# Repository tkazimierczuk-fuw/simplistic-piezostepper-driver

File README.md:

# A Simplistic Driver for Slip-Stick Piezo Positioners

This project presents a minimalistic, low-cost driver for slip-stick piezo positioners.

Conventional slip-stick piezo drivers typically rely on operational amplifiers to generate sawtooth waveforms. While this approach gives the most control over the stage, driving highly capacitive piezo loads with op-amps requires careful compensation and layout to avoid instability and self-oscillations.

In contrast, this driver avoids operational amplifiers altogether. Instead, the piezo load is driven directly using simple MOSFET stages. This significantly simplifies the circuit and improves robustness when dealing with capacitive loads, making the design well suited for ad-hoc, experimental, or budget-constrained setups.

The goal of this project is not ultimate performance, but practicality: providing a straightforward and reliable way to generate slip-stick drive signals with minimal component count and design overhead.

## Usage

The driver is straightforward - just connect your slip-stick piezo stage and use 3-way lever-switch to jog the stage. The step amplitude is fixed at 28 V and the step frequency is fixed (in the firmware) at 300 Hz. This values are suitable, e.g. for Attocube ANP series.

The circuit contains a PPTC resettable fuse which trips when we try to drive the short-circuit. It automatically resets upon switching the device off. 

## How it works

The driver generates the characteristic slip-stick waveform by charging and discharging the piezo capacitance directly through MOSFET switches, rather than through linear amplifiers. One stage provides a relatively slow voltage ramp (stick phase), while the other rapidly discharges the piezo (slip phase). Rapid charge/discharge is realized by linking the piezo to VCC/GND directly by a MOSFET. Slow ramp is realized by introducing an extra resistor R in series with the MOSFET. The time-constant of the slope is governed by a product of resistance R and the capacitance of the piezo stage.

Each of 3 modules has the same design:

## What to buy (typical components)

Exact values and footprints are given in the schematics/PCB files, but the design generally requires only common parts:

- 12x N-channel MOSFETs, e.g. STP55NF06L
- 6x half-bridge driver, e.g. IR2104STRPBF
- 3x BNC connector, e.g. R-128
- 3x lever switch, e.g. 1-1825139-8
- 1x power switch, e.g. R13-220BA-01-BBG (oversized)
- Raspberry Pico
- SMD 1206 elements: 7x diode, resistors: 1x 1MΩ, 6x 100kΩ, 12x 22Ω, 3x 10kΩ
- THT capacitors
- a polymer fuse, e.g. 0ZCJ0020FF2E
- DC supply socket, e.g. PJ-063AH
- step-up converter, e.g. MT3608 

## License & Disclaimer

This project is released under the MIT License. You are free to use, modify, and distribute it according to the terms of that license.

The design is provided as-is, without any warranties or guarantees of performance, safety, or suitability for any particular purpose. This is a research/DIY project; use it at your own risk.

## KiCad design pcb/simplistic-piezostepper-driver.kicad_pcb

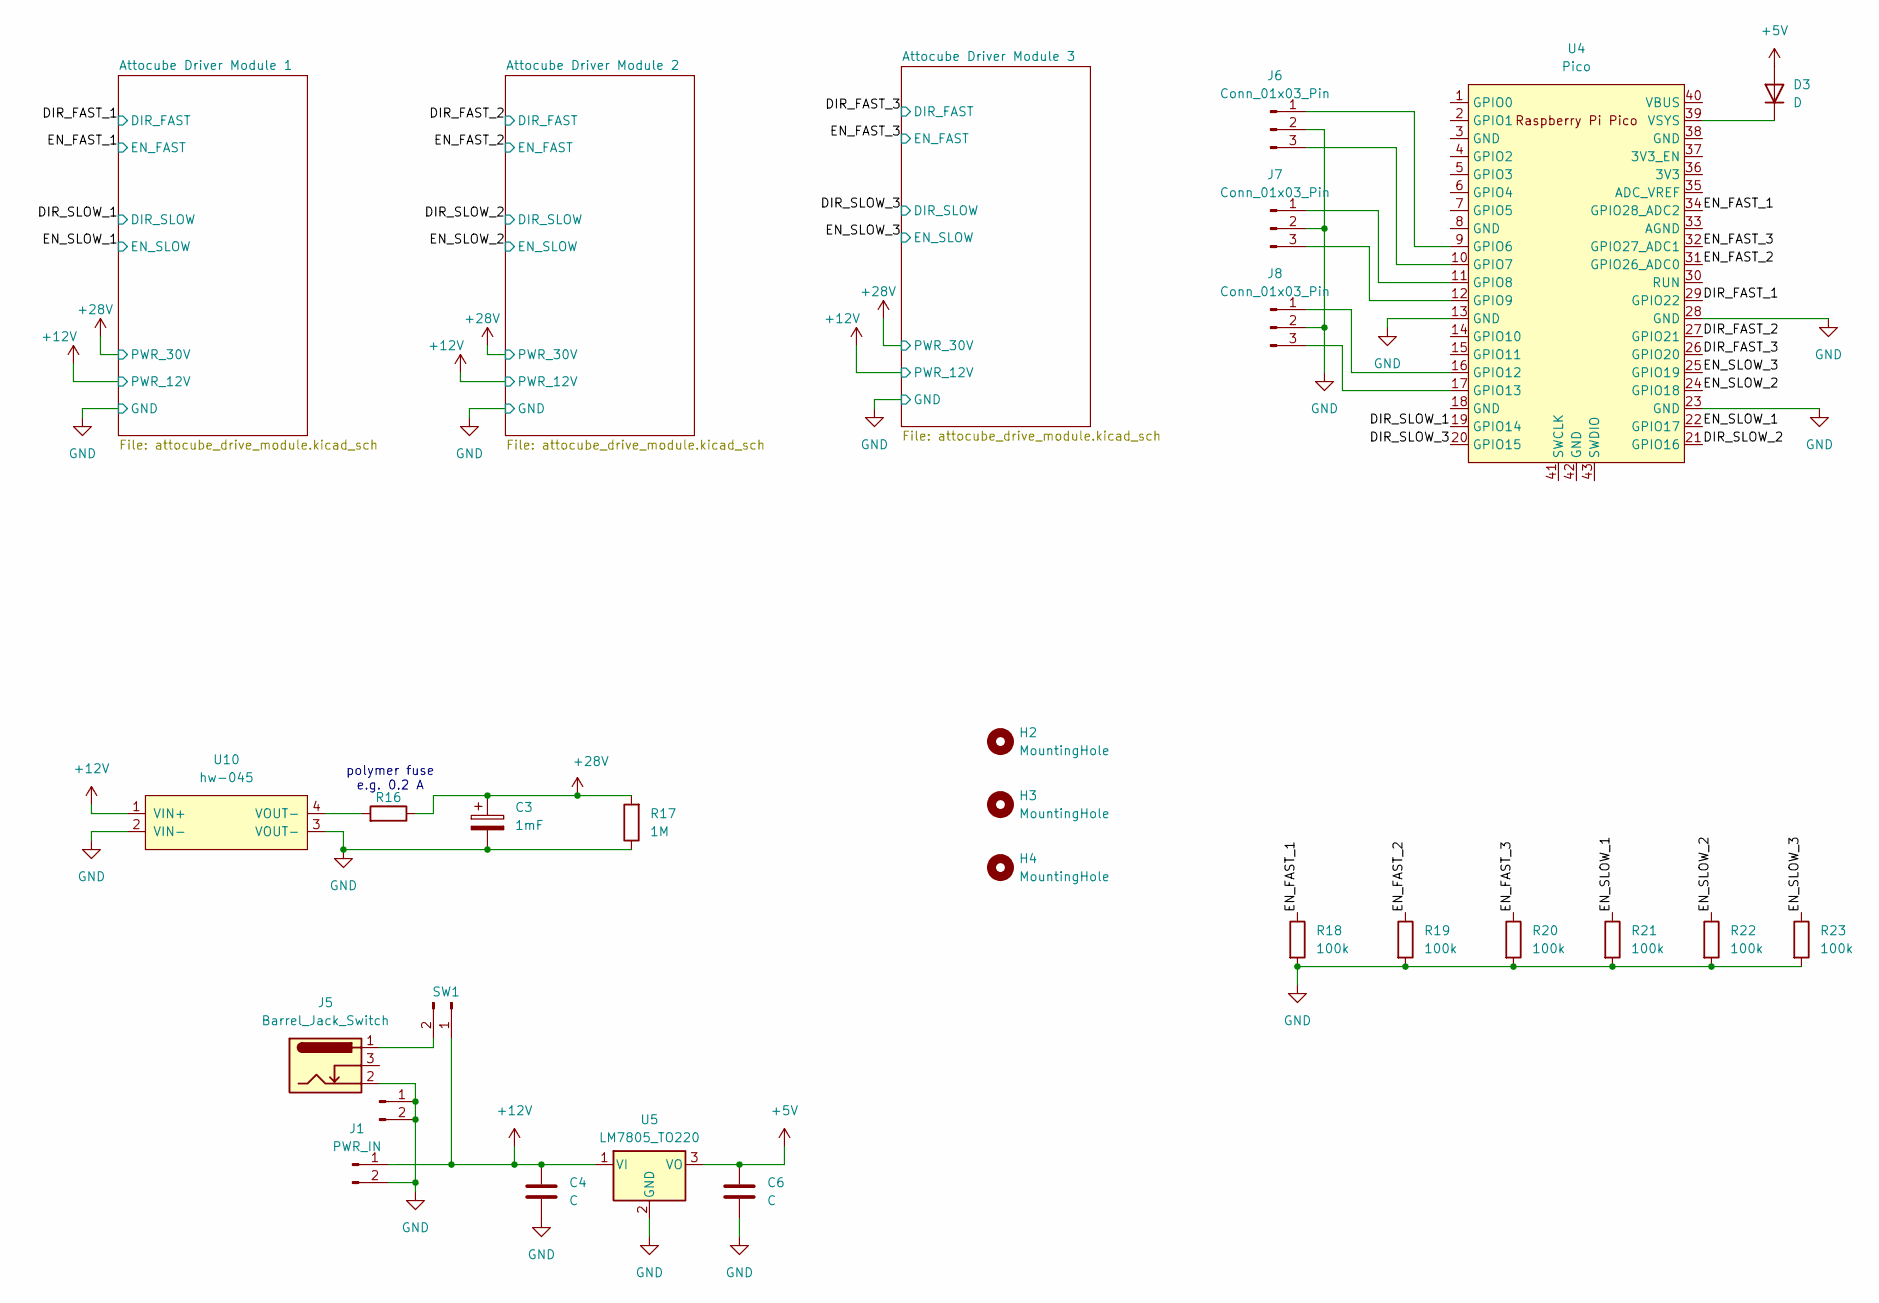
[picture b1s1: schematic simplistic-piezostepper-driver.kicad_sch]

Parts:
C3: 1mF; CP_Radial_D5.0mm_P2.00mm
C4, C6: C; C_Rect_L7.0mm_W3.5mm_P5.00mm
D3: D; D_1206_3216Metric_Pad1.42x1.75mm_HandSolder
H2, H3, H4: MountingHole; MountingHole_3.2mm_M3_Pad
J1: PWR_IN; SolderWire-0.1sqmm_1x02_P3.6mm_D0.4mm_OD1mm
J5: Barrel_Jack_Switch; BarrelJack_CUI_PJ-063AH_Horizontal
J6, J7, J8: Conn_01x03_Pin; PinHeader_1x03_P2.54mm_Vertical
J10: Conn_01x02_Pin; SolderWire-0.1sqmm_1x02_P3.6mm_D0.4mm_OD1mm
R16: 10?; R_1206_3216Metric_Pad1.30x1.75mm_HandSolder
R17: 1M; R_1206_3216Metric_Pad1.30x1.75mm_HandSolder
R18, R19, R20, R21, R22, R23: 100k; R_1206_3216Metric_Pad1.30x1.75mm_HandSolder
SW1: Conn_01x02_Pin; SolderWire-0.1sqmm_1x02_P3.6mm_D0.4mm_OD1mm
U4: Pico; RPi_Pico_SMD_TH
U5: LM7805_TO220; TO-220-3_Vertical
U10: hw-045

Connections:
+5V: C6.1, D3.2 (A), U5.3 (VO)
+12V: C4.1, J1.1, SW1.1, U5.1 (VI), U10.1 (VIN+); also elsewhere on the board
+28V: C3.1, R16.1, R17.2; also elsewhere on the board
/DIR_FAST_1: U4.29 (GPIO22); also elsewhere on the board
/DIR_FAST_2: U4.27 (GPIO21); also elsewhere on the board
/DIR_FAST_3: U4.26 (GPIO20); also elsewhere on the board
/DIR_SLOW_1: U4.19 (GPIO14); also elsewhere on the board
/DIR_SLOW_2: U4.21 (GPIO16); also elsewhere on the board
/DIR_SLOW_3: U4.20 (GPIO15); also elsewhere on the board
/EN_FAST_1: R18.1, U4.34 (GPIO28_ADC2); also elsewhere on the board
/EN_FAST_2: R19.1, U4.31 (GPIO26_ADC0); also elsewhere on the board
/EN_FAST_3: R20.1, U4.32 (GPIO27_ADC1); also elsewhere on the board
/EN_SLOW_1: R21.1, U4.22 (GPIO17); also elsewhere on the board
/EN_SLOW_2: R22.1, U4.24 (GPIO18); also elsewhere on the board
/EN_SLOW_3: R23.1, U4.25 (GPIO19); also elsewhere on the board
GND: C3.2, C4.2, C6.2, J1.2, J5.2, J6.2, J7.2, J8.2, J10.1, J10.2, R17.1, R18.2, R19.2, R20.2, R21.2, R22.2, R23.2, U4.13 (GND), U4.23 (GND), U4.28 (GND), U5.2 (GND), U10.2 (VIN-), U10.3 (VOUT-); also elsewhere on the board
unnamed: D3.1 (K), U4.39 (VSYS)
unnamed: J6.1, U4.9 (GPIO6)
unnamed: J6.3, U4.10 (GPIO7)
unnamed: J7.1, U4.11 (GPIO8)
unnamed: J7.3, U4.12 (GPIO9)
unnamed: J8.1, U4.16 (GPIO12)
unnamed: J8.3, U4.17 (GPIO13)
unnamed: R16.2, U10.4 (VOUT-)
unnamed: J5.1, SW1.2

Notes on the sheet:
polymer fuse e.g. 0.2 A

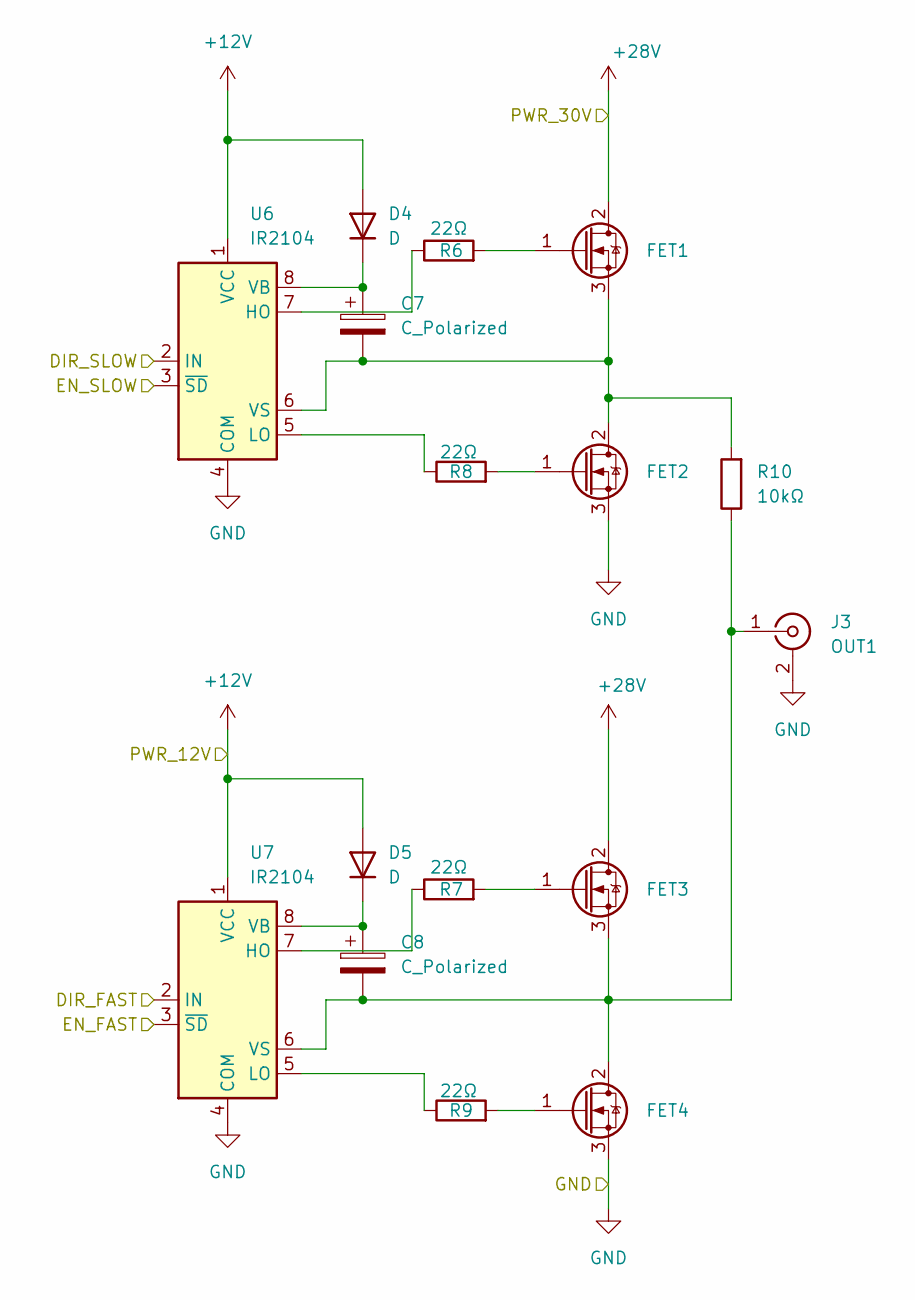
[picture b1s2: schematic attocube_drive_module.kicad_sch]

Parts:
C7, C8: C_Polarized; CP_Radial_D5.0mm_P2.00mm
D4, D5: D; D_1206_3216Metric_Pad1.42x1.75mm_HandSolder
FET1, FET2, FET3, FET4: Q_NMOS_Depletion_GDS; TO-220-3_Vertical
J3: OUT1; BNC_Amphenol_B6252HB-NPP3G-50_Horizontal
R6, R7, R8, R9: 22Ω; R_1206_3216Metric_Pad1.30x1.75mm_HandSolder
R10: 10kΩ; R_1206_3216Metric_Pad1.30x1.75mm_HandSolder
U6, U7: IR2104; SOIC-8_3.9x4.9mm_P1.27mm

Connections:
+12V: D4.2 (A), D5.2 (A), U6.1 (VCC), U7.1 (VCC); also elsewhere on the board
+28V: FET1.2 (D), FET3.2 (D); also elsewhere on the board
/DIR_FAST_1: U7.2 (IN); also elsewhere on the board
/DIR_SLOW_1: U6.2 (IN); also elsewhere on the board
/EN_FAST_1: U7.3 (~SD); also elsewhere on the board
/EN_SLOW_1: U6.3 (~SD); also elsewhere on the board
GND: FET2.3 (S), FET4.3 (S), J3.2 (Ext), U6.4 (COM), U7.4 (COM); also elsewhere on the board
unnamed: C7.1, D4.1 (K), U6.8 (VB)
unnamed: C8.1, D5.1 (K), U7.8 (VB)
unnamed: FET1.1 (G), R6.2
unnamed: C7.2, FET1.3 (S), FET2.2 (D), R10.2, U6.6 (VS)
unnamed: FET2.1 (G), R8.2
unnamed: FET3.1 (G), R7.2
unnamed: C8.2, FET3.3 (S), FET4.2 (D), J3.1 (In), R10.1, U7.6 (VS)
unnamed: FET4.1 (G), R9.2
unnamed: R6.1, U6.7 (HO)
unnamed: R8.1, U6.5 (LO)
unnamed: R7.1, U7.7 (HO)
unnamed: R9.1, U7.5 (LO)

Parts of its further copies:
C1, C2, C11, C12: C_Polarized; CP_Radial_D5.0mm_P2.00mm
D1, D2, D6, D7: D; D_1206_3216Metric_Pad1.42x1.75mm_HandSolder
FET5, FET6, FET7, FET8, FET9, FET10, FET11, FET12: Q_NMOS_Depletion_GDS; TO-220-3_Vertical
J2, J4: OUT1; BNC_Amphenol_B6252HB-NPP3G-50_Horizontal
R1, R2, R3, R4, R11, R12, R13, R14: 22Ω; R_1206_3216Metric_Pad1.30x1.75mm_HandSolder
R5, R15: 10kΩ; R_1206_3216Metric_Pad1.30x1.75mm_HandSolder
U1, U2, U8, U9: IR2104; SOIC-8_3.9x4.9mm_P1.27mm

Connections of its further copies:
+12V: D1.2 (A), D2.2 (A), D6.2 (A), D7.2 (A), U1.1 (VCC), U2.1 (VCC), U8.1 (VCC), U9.1 (VCC); also elsewhere on the board
+28V: FET5.2 (D), FET7.2 (D), FET9.2 (D), FET11.2 (D); also elsewhere on the board
/DIR_FAST_2: U2.2 (IN); also elsewhere on the board
/DIR_FAST_3: U9.2 (IN); also elsewhere on the board
/DIR_SLOW_2: U1.2 (IN); also elsewhere on the board
/DIR_SLOW_3: U8.2 (IN); also elsewhere on the board
/EN_FAST_2: U2.3 (~SD); also elsewhere on the board
/EN_FAST_3: U9.3 (~SD); also elsewhere on the board
/EN_SLOW_2: U1.3 (~SD); also elsewhere on the board
/EN_SLOW_3: U8.3 (~SD); also elsewhere on the board
GND: FET6.3 (S), FET8.3 (S), FET10.3 (S), FET12.3 (S), J2.2 (Ext), J4.2 (Ext), U1.4 (COM), U2.4 (COM), U8.4 (COM), U9.4 (COM); also elsewhere on the board
unnamed: C1.1, D1.1 (K), U1.8 (VB)
unnamed: C2.1, D2.1 (K), U2.8 (VB)
unnamed: C11.1, D6.1 (K), U8.8 (VB)
unnamed: C12.1, D7.1 (K), U9.8 (VB)
unnamed: FET5.1 (G), R1.2
unnamed: C1.2, FET5.3 (S), FET6.2 (D), R5.2, U1.6 (VS)
unnamed: FET6.1 (G), R3.2
unnamed: FET7.1 (G), R2.2
unnamed: C2.2, FET7.3 (S), FET8.2 (D), J2.1 (In), R5.1, U2.6 (VS)
unnamed: FET8.1 (G), R4.2
unnamed: FET9.1 (G), R11.2
unnamed: C11.2, FET9.3 (S), FET10.2 (D), R15.2, U8.6 (VS)
unnamed: FET10.1 (G), R13.2
unnamed: FET11.1 (G), R12.2
unnamed: C12.2, FET11.3 (S), FET12.2 (D), J4.1 (In), R15.1, U9.6 (VS)
unnamed: FET12.1 (G), R14.2
unnamed: R1.1, U1.7 (HO)
unnamed: R3.1, U1.5 (LO)
unnamed: R2.1, U2.7 (HO)
unnamed: R4.1, U2.5 (LO)
unnamed: R11.1, U8.7 (HO)
unnamed: R13.1, U8.5 (LO)
unnamed: R12.1, U9.7 (HO)
unnamed: R14.1, U9.5 (LO)

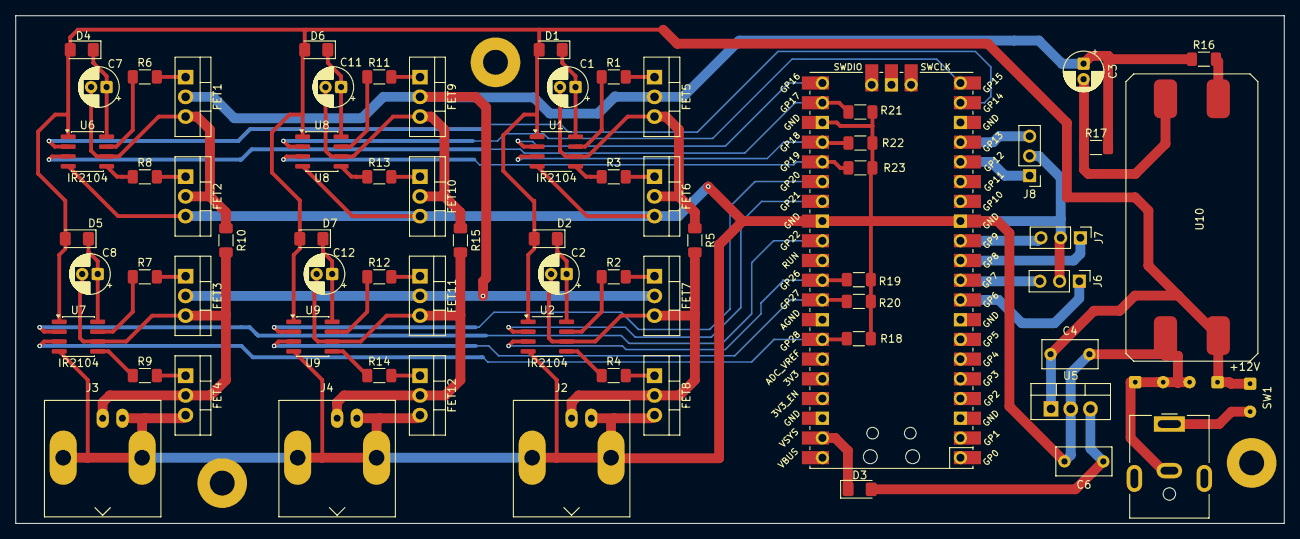
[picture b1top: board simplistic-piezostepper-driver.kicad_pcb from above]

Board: 2 copper layers, 163.4 x 65.4 mm, 73 parts (0 on the bottom side), 61 nets.

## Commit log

2026-02-01 Added a KiCAD schematic
2026-02-02 Updated description
2026-02-02 Uploaded: firmware and case 3D model
